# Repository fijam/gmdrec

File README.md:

## Overview
gmdrec records and labels tracks on selected Sony portable MD recorders.

Compatible models include: R55, R37, R70, R90, R91, R700, R701, R900, N707, R909, R910, N1, N707

**Note:** R909, R910 and N1 **require** 100k Ohm pulldown on the LCD data line. This is applied automatically by the rev3 hardware. Rev2 has a solder bridge, on rev1 you need to [swap out the connector](https://github.com/fijam/gmdrec/wiki/Remote-connectors).

Need to be tested: G755, G750

[Quick start guide for Windows](https://github.com/fijam/gmdrec/wiki/Quick-Start-Guide)

[Quick start guide for Linux](https://github.com/fijam/gmdrec/wiki/Linux-setup)

## Demo

## How it works

You need:

- [Foobar2000](https://www.foobar2000.org/) (Windows) or [DeaDBeeF](https://deadbeef.sourceforge.io/) (Linux/macOS) music player
- [beefweb](https://github.com/hyperblast/beefweb) plugin for the music player
- an interface circuit that emulates the remote (see below)

gmdrec uses an API provided by the beefweb plugin to remotely control a music player. It grabs the track names from a playlist and breaks them down into a sequence of buttons to press. These are translated by the interface circuit into signals recognized by the MD recorder.

### Interface circuit

The circuit comprises a USB-I2C bridge and a I2C digital potentiometer as well as a few passive components. 

The schematics and PCB files are provided in the hardware directory. You can get a preassembled one from me directly.

### Software

**[Feature overview](https://github.com/fijam/gmdrec/wiki/Feature-overview)**  

**label**: Specify how the tracks should be formatted. You can use any combination of fields from [here](https://wiki.hydrogenaud.io/index.php?title=Foobar2000:Title_Formatting_Reference#Remapped_metadata_fields).

**recorder**: Select your recorder model. Note that some devices may [behave differently depending on firmware](https://github.com/fijam/gmdrec/wiki/Troubleshooting#firmware-revisions).

**disc_title**: Optionally, the disc can be labelled with an album title.

**lang_code**: By default, gmdrec will attempt to transliterate non-latin scripts. As some languages share the same characters (e.g. Japanese and Chinese) you can specify a [two-letter language code](https://en.wikipedia.org/wiki/List_of_ISO_639-1_codes) to make it more accurate.

**label_mode**: Optionally, you can use gmdrec to label a disc which has been already recorded. Make sure the number of items on the playlist equals the number of tracks on the MD and set the recorder to the first track to be labelled. If you select `ERASE`, old track names will be deleted before labelling.

**no_tmarks**: By default, gmdrec will insert a Track Mark at the end of every track. This option adds 2 seconds of silence between each track and adding track marks is left to the recorder. *Strongly recommended for R909/R910/N1.*

**--ignore-gooey**: Optionally, you can run the software directly in console without the GUI.

### Recording a MiniDisc

1. Create a playlist you want to record.
2. Connect your PC audio output (toslink or analog) to the input on the MD recorder.
3. Connect the interface circuit to USB and to the remote connector on the MD recorder.
4. Start gmdrec.

## Linux

gmdrec works on GNU/Linux but requires some additional setup. Instructions are [on a separate wiki page.](https://github.com/fijam/gmdrec/wiki/Linux-setup)

## Limitations

Limitations of the MD format:

- up to 254 tracks per disk
- up to ~200 characters per track
- up to ~1700 total characters per disc
- limited character set: ASCII charaters excluding `[ \ ] ^ { | } ~`

gmdrec will fail if track duration is too short to finish labelling in time. It takes about 35 seconds to label a track. If you have a disc with many short tracks, consider recording it first and then using **label_mode** which pauses each track for labelling.

## Contributions welcome

Merge requests providing new functionality or support for additional devices are welcome. 

### Note: if you are looking for the older version of this project which relied on a Raspberry Pi, check out https://github.com/fijam/md-rec/

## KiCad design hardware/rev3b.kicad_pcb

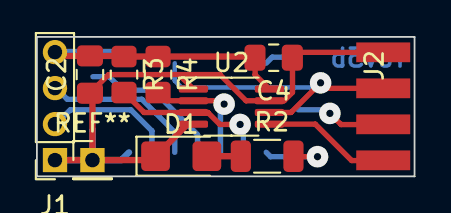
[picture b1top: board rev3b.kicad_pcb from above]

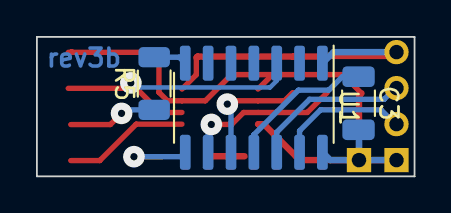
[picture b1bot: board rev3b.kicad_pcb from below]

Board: 2 copper layers, 21.0 x 7.7 mm, 12 parts (3 on the bottom side), 13 nets.

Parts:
C2: 0.1uF; C_0805_2012Metric_Pad1.18x1.45mm_HandSolder
C3: 0.33uF; C_1206_3216Metric
C4: 0.3uF; C_0805_2012Metric_Pad1.18x1.45mm_HandSolder
D1: LED; LED_1206_3216Metric_Castellated
J1: Conn_01x04; PinSocket_1x04_P2.00mm_Vertical
J2: Conn_01x04; Connector_Sony_Remote
R2: 360; R_1206_3216Metric
R3, R4: 3.3k; R_0805_2012Metric_Pad1.20x1.40mm_HandSolder
R5: 100k; R_1206_3216Metric
U1: MCP2221AxSL; SOIC-14_3.9x8.7mm_P1.27mm
U2: mcp4562; MSOP-8_3x3mm_P0.65mm

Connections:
+5V: C2.2, C4.2, J1.4, R3.1, R4.1, U1.1, U2.8
GND: C2.1, C3.2, C4.1, D1.1, J1.1, J2.1, U1.14, U2.1, U2.4, U2.7
unnamed: C3.1, U1.11
unnamed: D1.2, R2.1
unnamed: J1.2, U1.13
unnamed: J1.3, U1.12
unnamed: J2.2, U1.3, U2.6
unnamed: J2.3, R5.1
unnamed: J2.4, U2.5
unnamed: R2.2, U1.8
unnamed: R3.2, U1.9, U2.3
unnamed: R4.2, U1.10, U2.2
unnamed: R5.2, U1.7

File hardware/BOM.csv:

Id,Designator,Package,Quantity,Designation,Supplier and ref
1,J1,USB_Micro-B_Amphenol_10118192_Horizontal,1,USB-micro-B-8192,Amphenol 10118192-0001LF
2,C1,C_1210_3225Metric,1,10uF,
3,C2,C_1206_3216Metric,1,0.1uF,
4,C3,C_0805_2012Metric,1,0.33uF,
5,R,R_1206_3216Metric,2,3.3k,
6,U1,SOIC-14_3.9x8.7mm_P1.27mm,1,MCP2221AxSL,Microchip MCP2221(A)-I/SL
7,U2,SOT-23-8_Handsoldering,1,AD5245,Analog Devices AD5245BRJZ50 alternative: ONSEMI CAT5171TBI-50GT3
8,case,-,1,G1911C or MC001529,Gainta or MULTICOMP PRO

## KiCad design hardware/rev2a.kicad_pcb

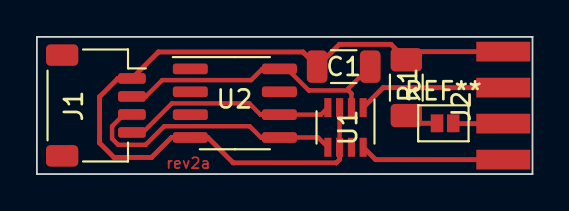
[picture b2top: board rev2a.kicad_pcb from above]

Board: 2 copper layers, 27.5 x 7.6 mm, 6 parts (0 on the bottom side), 7 nets.

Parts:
C1: 0.1; C_1206_3216Metric
J1: Conn_01x04; JST_SH_SM04B-SRSS-TB_1x04-1MP_P1.00mm_Horizontal
J2: 01x04; Connector_Sony_Remote
R1: R_1206_3216Metric_Pad1.30x1.75mm_HandSolder
U1: AD5245; SOT-23-8
U2: 24LC04; SOIC-8_3.9x4.9mm_P1.27mm

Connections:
GND: C1.2, J1.1, J2.1, R1.2, U1.3, U1.6, U2.4
unnamed: J2.2, U1.1
unnamed: J2.3, R1.1
unnamed: J2.4, U1.8
SCL: J1.4, U1.4, U2.6
SDA: J1.3, U1.5, U2.5
VCC: C1.1, J1.2, U1.2, U2.8

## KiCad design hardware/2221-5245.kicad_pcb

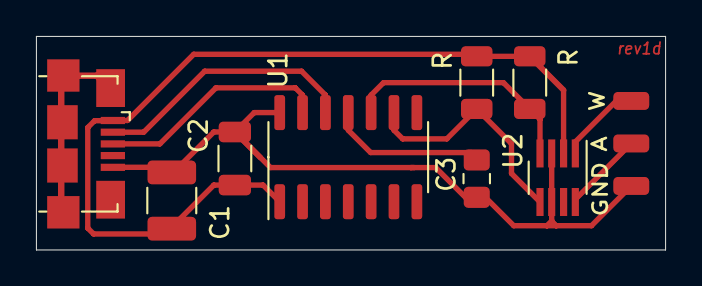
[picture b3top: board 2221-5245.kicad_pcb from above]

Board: 2 copper layers, 35.0 x 11.9 mm, 11 parts (0 on the bottom side), 9 nets.

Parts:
A: A; SolderWirePad_1x01_SMD_1x2mm
C1: 10uF; C_1210_3225Metric_Pad1.33x2.70mm_HandSolder
C2: 0.1uF; C_1206_3216Metric
C3: 0.33uF; C_0805_2012Metric_Pad1.18x1.45mm_HandSolder
GND: GND; SolderWirePad_1x01_SMD_1x2mm
J1: USB-micro-B-8192; USB_Micro-B_Amphenol_10118192_Horizontal
R: 3.3k; R_1206_3216Metric
R#2: 3.3k; R_1206_3216Metric
U1: MCP2221AxSL; SOIC-14_3.9x8.7mm_P1.27mm
U2: AD5245; SOT-23-8_Handsoldering
W: W; SolderWirePad_1x01_SMD_1x2mm

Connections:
+5V: C1.1, C2.1, J1.1, R.1, R#2.1, U1.1, U2.2
GND: C1.2, C2.2, C3.2, GND.1, J1.5, U1.14, U2.3, U2.6
unnamed: C3.1, U1.11
unnamed: J1.2, U1.12
unnamed: J1.3, U1.13
unnamed: A.1, U2.8
unnamed: U2.1, W.1
unnamed: R.2, U1.9, U2.5
unnamed: R#2.2, U1.10, U2.4

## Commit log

2021-10-10 add pycharm's .idea
2021-10-10 add IC datasheets
2021-10-10 Draft of README
2021-10-10 document --ignore-gooey
2021-10-10 Add images
2021-10-10 change semicolons to commas
2021-10-10 add a link to video demonstration
2021-10-10 add the polycarbonate case
2021-10-11 add requirements.txt (top-level)
2021-10-11 remove unused check
2021-10-11 add a function to replace some unsupported characters in titles
2021-10-11 formatting, phrasing
2021-10-11 link to Linux setup steps on the wiki
2021-10-14 break recorder definitions into separate files
2021-10-17 add a wiper value for the PLAYMODE button
2021-10-17 move user-accessible settings to a yaml file
2021-10-17 add a default selection for recorder model
2021-10-17 don't export the recorder var (for now, consider Dynamic values)
2021-10-17 settings file is going to be hardcoded
2021-10-21 change the way rec standby is entered to improve reliability
2021-10-21 change the way rec standby is entered to improve reliability - we follow the manual now
2021-11-03 Provide an option to erase old track names in label mode (hard-coded to 128 characters, about 8 seconds per track)
2021-11-03 Update footprints in kicad pcb file
2021-11-03 pin for pin replacement option for AD5245 from ONSEMI (CAT5171)
2021-11-03 Wait a bit longer before attempting to label disc title
2021-11-04 Refactor hw initialization so that we can shut down the digipot as soon as the app is launched, fixes #4
2021-11-06 honor the Erase mode when labelling the disc title
2021-11-08 simplify webapi.py use
2021-11-10 initial Spotify support
2021-11-20 weird JPN firmware behaviour fix #8
2021-11-21 add early JPN firmware devices as a separate selection fix #8
2021-11-21 link wiki on firmware versions
2021-11-22 initial support for R909/R910/N1 - needs pull down on LCD data line
2021-11-25 support R909/R910/N1 with Japanese firmware
2021-11-25 document support for R909/R910/N1
2021-11-25 Add a universal connector PCB file
2021-11-26 update universal connector pcb
2021-12-03 add datasheet for Onsemi replacement digipot
2021-12-15 identify active playlist, don't assume p1 ref #11
2021-12-15 Add support for MZ-R37
    The MZ-R37 works much the same as the R90 etc., but its character-set
    calculation basis differs, and the key sequence to enter labelling mode
    is different.
2022-02-23 Add pcb for the stemma qt accessory
2022-03-15 update recorder choices, separate r55/r37, remove early FW versions until refactor is done
2022-03-15 add support for R55/R37 (for real this time)
2022-03-27 add support for labelling tracks in katakana, move ascifyy from webapi to hardware
2022-03-27 break out R55/R37 into separate definitions, make the number of Stop presses to enter labelling device-specific
2022-03-27 actually 909 need two Stop presses
2022-03-27 update supported models, fixes #12
2022-03-27 first pass at implementing reading calibration data from EEPROM (rev2a boards)
2022-04-18 Remove settings.conf defaults. Add VolUp should we decide to use it later.
2022-04-18 Since we now print track names before passing them to asciify, make sure our console output is set to utf8 (thanks Windows)
2022-04-23 R55 and R37 need a small delay before we begin input.
2022-04-23 add some japanese punctuation to letter_replace()
2022-04-23 add VolUp to wipers read from eeprom
2022-04-23 eeprom wipers formatting
2022-04-23 rename hardware to logic as thats what it does
2022-04-23 rename digipot to hardware
2022-04-23 get rid of OFFSET
2022-04-23 move PRESS and HOLD to per-device definitions, move more stuff to logic.py
2022-04-23 flew too close to the Sun
2022-04-23 clean up string concatenation
2022-04-25 separate regular mode and labelling mode, fixes #15 (incidentally also sfixes a bug where tmarks were inserted in no_tmarks mode)
2022-04-25 get rid of play_and_pause() (used just once)
2022-04-25 clean up and simplify track sanitization, fixes #19
2022-04-25 fix a brainfart in set_player (harmless but still)
2022-04-25 do sanitize_tracklist with list comprehension, flip write_toc and set_player on Ctrl-C
2022-04-27 move eeprom stuff from logic to hardware
2022-04-27 slowpokes need more than 10s to save ToC after all
2022-04-28 removing the look-up table for charset switching
2022-04-28 formatting
2022-04-28 Add an 'about' dialog including version number and license
2022-04-30 updating some dependencies, bumping up requirements
2022-05-01 bumping up requirements some more
2022-05-01 hardware refactor part 1, todo: eeproms
2022-05-01 hardware refactor part 2
2022-05-01 "zip it! ziiiip." - Dr. Evil
2022-05-09 prepare to introduce logging, refactor wipers_from_eeprom a little
2022-05-09 increase default height a bit to get rid of scrollbar
2022-05-09 replace header comments with docstrings
2022-05-09 roll reset_pulldown into pulldown_on_data
2022-05-10 hardcode server_url (a leftover from RPi days really)
2022-05-10 remove spotify support in favour of a foobar plugin
2022-05-10 more docstrings
2022-05-10 fix an ugly typo
2022-05-10 put the version string on top, follow PEP 440
2022-05-10 move push_button() & deal with wipers only in hardware.py
2022-05-10 clean up imports
2022-05-10 update the GUI
2022-05-10 remove things no longer needed from settings.conf
2022-05-10 fix a brainfart following lang_code change
2022-05-11 remove spotipy from requirements
2022-05-11 move cleanup_exit to hardware.py
2022-05-13 Add resistor values documentation
2022-05-13 Direct Linux I2C access + Gtk button GUI example
2022-05-13 explain calibration and reference values in yaml comment, shuffle the dict in the same order
2022-06-16 Increase button press time to 50ms for all devices
2022-06-18 fix a typo in settings comment
2022-06-18 redo hardware initialization based on content of status register on mcp4562
2022-06-18 move shutdown_pot to try-else, bump to 0.7b5
2022-06-19 Add PCB for rev3 of the board
2022-10-02 Allow for playlists that don't specify track duration (#13)
2022-10-02 Bump point release
2022-10-04 add a missing f-string
2022-10-04 Rename 2221-5245.kicad_pcb to rev1c.kicad_pcb
2022-10-04 Rename md-rec-qwiic.kicad_pcb to rev2a.kicad_pcb
2022-10-04 Rename md-rec-rev3b-ds - ver5.1.kicad_pcb to rev3b.kicad_pcb
2022-10-04 Add schematics for rev3
2022-10-04 rename schematics for rev1
2023-02-05 Add backslash to replacement map, add a catch-all clause for replacing unknown characters.
2023-02-05 bump version to 0.7.2
2023-05-02 document how rev3 board detection works since I never remember
2024-02-23 hack in our pot
2024-03-04 added more logging
2025-06-16 fix typo in error message on endpoint timeout
2025-06-16 documenting rev3b hw revision
2025-07-07 Update README.md
    update screenshot, link Feature overview page
2025-07-07 Update README.md
    Correct link for quick start guide
2025-10-26 Update hidapi version, add pyyaml
2025-10-26 Add pyinstaller spec file, make it happy
2025-10-26 Add unihandecode data explicitly to spec
2025-10-30 Re-add support for early R90 JPN firmware (attempt 1)
2026-01-12 Update requirements.txt
    Raising hidapi requirements now that 0.15.0 was released and actually builds
2026-02-03 Create n910.py
    PoC for emulating RM-MC33/35/38 remotes for MZ-N910
